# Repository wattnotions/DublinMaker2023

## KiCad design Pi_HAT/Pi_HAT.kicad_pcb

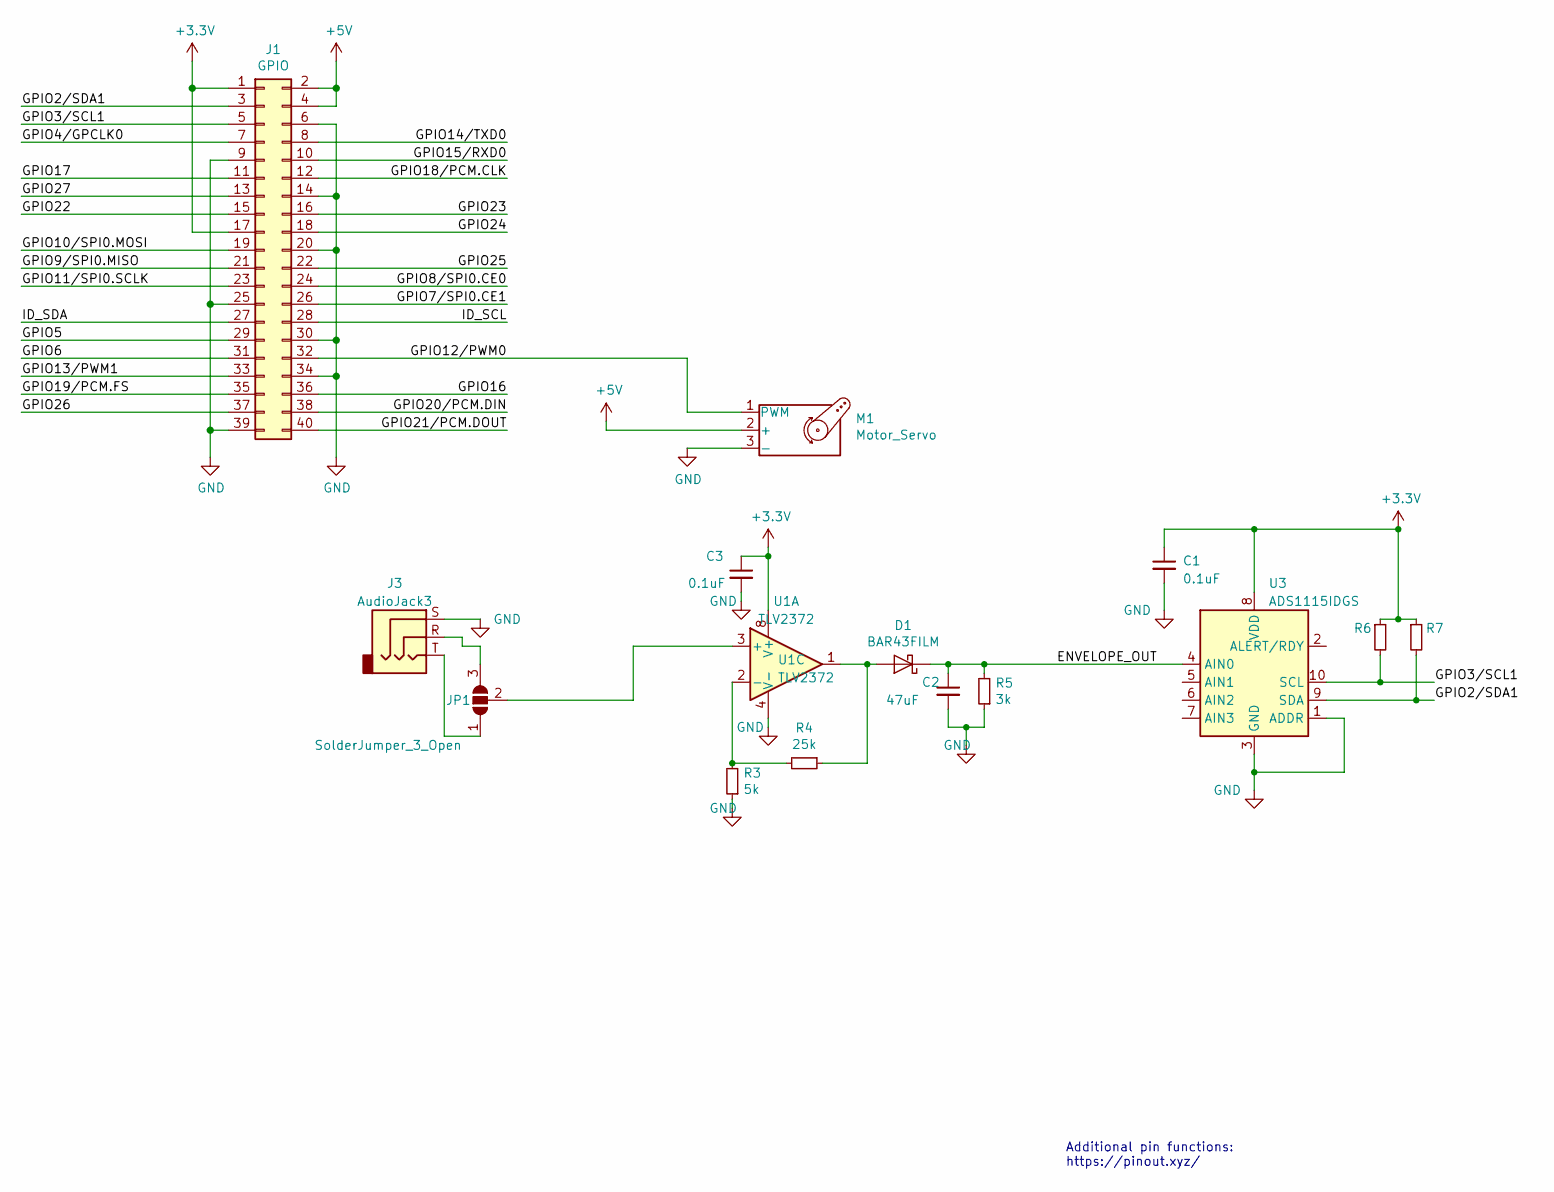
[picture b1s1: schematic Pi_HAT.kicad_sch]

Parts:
C1, C3: 0.1uF; C_0603_1608Metric_Pad1.08x0.95mm_HandSolder
C2: 47uF; C_1206_3216Metric
D1: BAR43FILM; SOT-23
J1: GPIO; PinSocket_2x20_P2.54mm_Vertical
J3: AudioJack3; Jack_3.5mm_CUI_SJ-3523-SMT_Horizontal
JP1: SolderJumper_3_Open; SolderJumper-3_P2.0mm_Open_TrianglePad1.0x1.5mm_NumberLabels
M1: Motor_Servo; JST_PH_S3B-PH-K_1x03_P2.00mm_Horizontal
R3: 5k; R_0603_1608Metric
R4: 25k; R_0603_1608Metric
R5: 3k; R_0603_1608Metric
R6, R7: R_Small; R_0402_1005Metric_Pad0.72x0.64mm_HandSolder
U1: TLV2372; SOIC-8_3.9x4.9mm_P1.27mm
U3: ADS1115IDGS; TSSOP-10_3x3mm_P0.5mm

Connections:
+3V3: C1.1, C3.1, J1.1, J1.17, R6.1, R7.1, U1.8 (V+), U3.8 (VDD)
+5V: J1.2, J1.4, M1.2 (+)
/ENVELOPE_OUT: C2.1, D1.3 (K), R5.2, U3.4 (AIN0)
/GPIO2/SDA1: J1.3, R7.2, U3.9 (SDA)
/GPIO3/SCL1: J1.5, R6.2, U3.10 (SCL)
/GPIO4/GPCLK0: J1.7
/GPIO5: J1.29
/GPIO6: J1.31
/GPIO7/SPI0.CE1: J1.26
/GPIO8/SPI0.CE0: J1.24
/GPIO9/SPI0.MISO: J1.21
/GPIO10/SPI0.MOSI: J1.19
/GPIO11/SPI0.SCLK: J1.23
/GPIO12/PWM0: J1.32, M1.1 (PWM)
/GPIO13/PWM1: J1.33
/GPIO14/TXD0: J1.8
/GPIO15/RXD0: J1.10
/GPIO16: J1.36
/GPIO17: J1.11
/GPIO18/PCM.CLK: J1.12
/GPIO19/PCM.FS: J1.35
/GPIO20/PCM.DIN: J1.38
/GPIO21/PCM.DOUT: J1.40
/GPIO22: J1.15
/GPIO23: J1.16
/GPIO24: J1.18
/GPIO25: J1.22
/GPIO26: J1.37
/GPIO27: J1.13
/ID_SCL: J1.28
/ID_SDA: J1.27
GND: C1.2, C2.2, C3.2, J1.6, J1.9, J1.14, J1.20, J1.25, J1.30, J1.34, J1.39, J3.S, M1.3 (-), R3.1, R5.1, U1.4 (V-), U3.1 (ADDR), U3.3 (GND)
unnamed: D1.1 (A), R4.1, U1.1
unnamed: J3.T, JP1.1 (A)
unnamed: J3.R, JP1.3 (B)
unnamed: JP1.2 (C), U1.3 (+)
unnamed: R3.2, R4.2, U1.2 (-)

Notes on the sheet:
Additional pin functions: https://pinout.xyz/

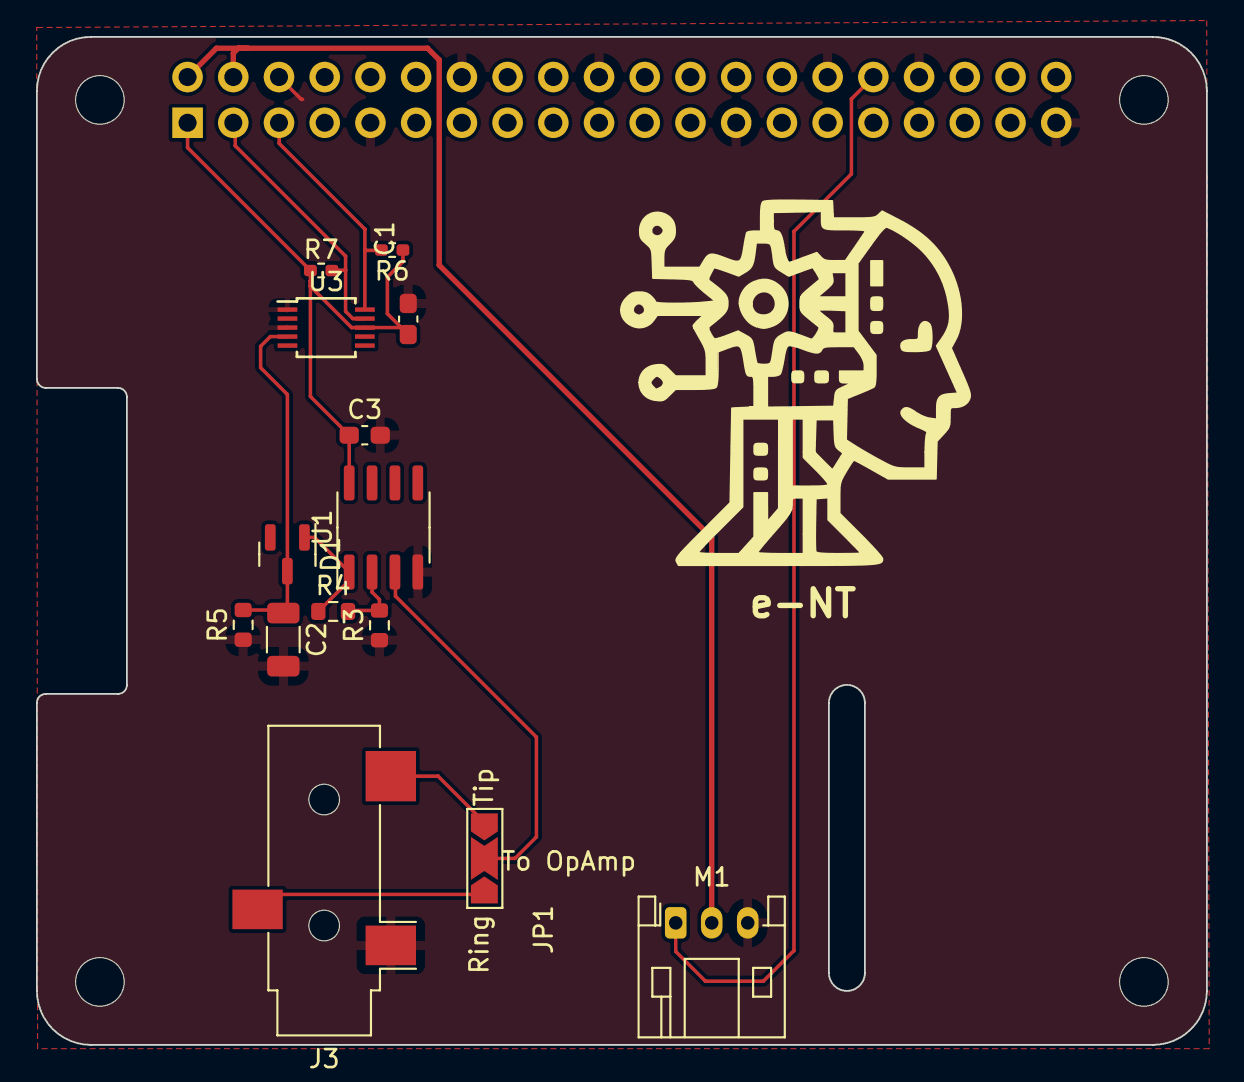
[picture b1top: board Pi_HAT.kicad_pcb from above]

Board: 2 copper layers, 65.0 x 56.0 mm, 19 parts (1 on the bottom side), 12 nets.

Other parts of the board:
MH1, MH2, MH3, MH4: MountingHole_2.7mm_M2.5

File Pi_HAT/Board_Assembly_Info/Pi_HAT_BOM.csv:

"Source:","C:\Users\ShaneOrmonde\Documents\GitHub\DublinMaker2023\Pi_HAT\Pi_HAT.kicad_sch"
"Date:","13/04/2023 16:50:31"
"Tool:","Eeschema (7.0.0)"
"Generator:","C:\Program Files\KiCad\6.0\bin\scripting\plugins/bom_csv_grouped_by_value.py"
"Component Count:","15"

"Individual Components:"

"Item","Qty","Reference(s)","Value","LibPart","Footprint","Datasheet"
"","","C1","0.1uF","Device:C_Small","Capacitor_SMD:C_0603_1608Metric_Pad1.08x0.95mm_HandSolder","~"
"","","C2","47uF","Device:C_Small","Capacitor_SMD:C_1206_3216Metric","~"
"","","C3","0.1uF","Device:C_Small","Capacitor_SMD:C_0603_1608Metric_Pad1.08x0.95mm_HandSolder","~"
"","","D1","BAR43FILM","Alexa_kicad_PCB-rescue:BAR43FILM-Diode","Package_TO_SOT_SMD:SOT-23","www.st.com/resource/en/datasheet/bar43.pdf"
"","","J1","GPIO","Connector_Generic:Conn_02x20_Odd_Even","Connector_PinSocket_2.54mm:PinSocket_2x20_P2.54mm_Vertical","~"
"","","J3","AudioJack3","Connector_Audio:AudioJack3","Connector_Audio:Jack_3.5mm_CUI_SJ-3523-SMT_Horizontal","~"
"","","JP1","SolderJumper_3_Open","Jumper:SolderJumper_3_Open","Jumper:SolderJumper-3_P2.0mm_Open_TrianglePad1.0x1.5mm_NumberLabels","~"
"","","M1","Motor_Servo","Motor:Motor_Servo","Connector_JST:JST_PH_S3B-PH-K_1x03_P2.00mm_Horizontal","http://forums.parallax.com/uploads/attachments/46831/74481.png"
"","","R3","5k","Device:R_Small","Resistor_SMD:R_0603_1608Metric","~"
"","","R4","25k","Device:R_Small","Resistor_SMD:R_0603_1608Metric","~"
"","","R5","3k","Device:R_Small","Resistor_SMD:R_0603_1608Metric","~"
"","","R6","R_Small","Device:R_Small","Resistor_SMD:R_0402_1005Metric_Pad0.72x0.64mm_HandSolder","~"
"","","R7","R_Small","Device:R_Small","Resistor_SMD:R_0402_1005Metric_Pad0.72x0.64mm_HandSolder","~"
"","","U1","TLV2372","Amplifier_Operational:TLV2372","Package_SO:SOIC-8_3.9x4.9mm_P1.27mm","http://www.ti.com/lit/ds/symlink/tlv2375.pdf"
"","","U3","ADS1115IDGS","Analog_ADC:ADS1115IDGS","Package_SO:TSSOP-10_3x3mm_P0.5mm","http://www.ti.com/lit/ds/symlink/ads1113.pdf"



"Collated Components:"

"Item","Qty","Reference(s)","Value","LibPart","Footprint","Datasheet"
"1","2","C1, C3","0.1uF","Device:C_Small","Capacitor_SMD:C_0603_1608Metric_Pad1.08x0.95mm_HandSolder","~"
"2","1","C2","47uF","Device:C_Small","Capacitor_SMD:C_1206_3216Metric","~"
"3","1","D1","BAR43FILM","Alexa_kicad_PCB-rescue:BAR43FILM-Diode","Package_TO_SOT_SMD:SOT-23","www.st.com/resource/en/datasheet/bar43.pdf"
"4","1","J1","GPIO","Connector_Generic:Conn_02x20_Odd_Even","Connector_PinSocket_2.54mm:PinSocket_2x20_P2.54mm_Vertical","~"
"5","1","J3","AudioJack3","Connector_Audio:AudioJack3","Connector_Audio:Jack_3.5mm_CUI_SJ-3523-SMT_Horizontal","~"
"6","1","JP1","SolderJumper_3_Open","Jumper:SolderJumper_3_Open","Jumper:SolderJumper-3_P2.0mm_Open_TrianglePad1.0x1.5mm_NumberLabels","~"
"7","1","M1","Motor_Servo","Motor:Motor_Servo","Connector_JST:JST_PH_S3B-PH-K_1x03_P2.00mm_Horizontal","http://forums.parallax.com/uploads/attachments/46831/74481.png"
"8","1","R3","5k","Device:R_Small","Resistor_SMD:R_0603_1608Metric","~"
"9","1","R4","25k","Device:R_Small","Resistor_SMD:R_0603_1608Metric","~"
"10","1","R5","3k","Device:R_Small","Resistor_SMD:R_0603_1608Metric","~"
"11","2","R6, R7","R_Small","Device:R_Small","Resistor_SMD:R_0402_1005Metric_Pad0.72x0.64mm_HandSolder","~"
"12","1","U1","TLV2372","Amplifier_Operational:TLV2372","Package_SO:SOIC-8_3.9x4.9mm_P1.27mm","http://www.ti.com/lit/ds/symlink/tlv2375.pdf"
"13","1","U3","ADS1115IDGS","Analog_ADC:ADS1115IDGS","Package_SO:TSSOP-10_3x3mm_P0.5mm","http://www.ti.com/lit/ds/symlink/ads1113.pdf"

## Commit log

2023-02-08 added example scripts
2023-03-26 fixed bug and changed voice to scottish accent
2023-03-26 Updated test scripts for debugging hw issues on raspi
2023-04-12 sch done, pcb started
2023-04-12 sch and pcb done
2023-04-13 added some final bits - silk etc
2023-05-13 added PCB and other shit
2023-05-15 added adc to pwm realistic mouth movement code
2023-08-12 test
2023-08-12 added .env to gitignore
2023-08-26 latest stuff
2023-08-26 removed api key from git
2023-08-26 working eyes conrtoller class
2023-08-26 basic eye tracking working
2023-08-26 fist working full test, voice, eye tracking etc
2023-08-27 basic cam face tracker with x,y output example
2023-08-27 basic idle script with q's working
2023-09-01 added start bash that hides errors
2023-09-01 added option to use whisper api for voice recog
2023-09-02 added token limit check
